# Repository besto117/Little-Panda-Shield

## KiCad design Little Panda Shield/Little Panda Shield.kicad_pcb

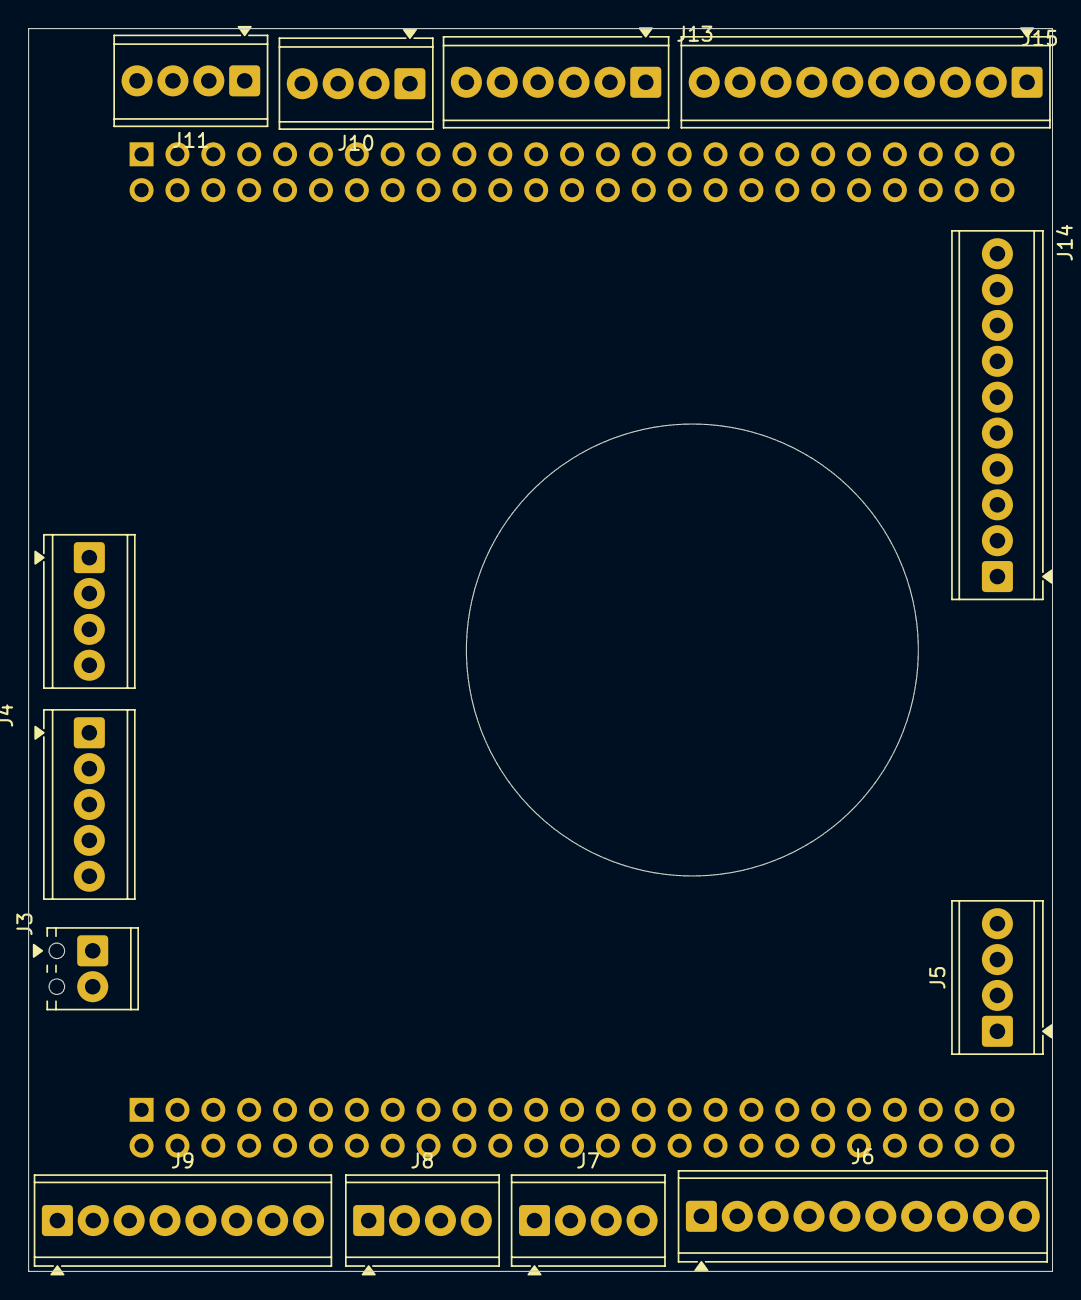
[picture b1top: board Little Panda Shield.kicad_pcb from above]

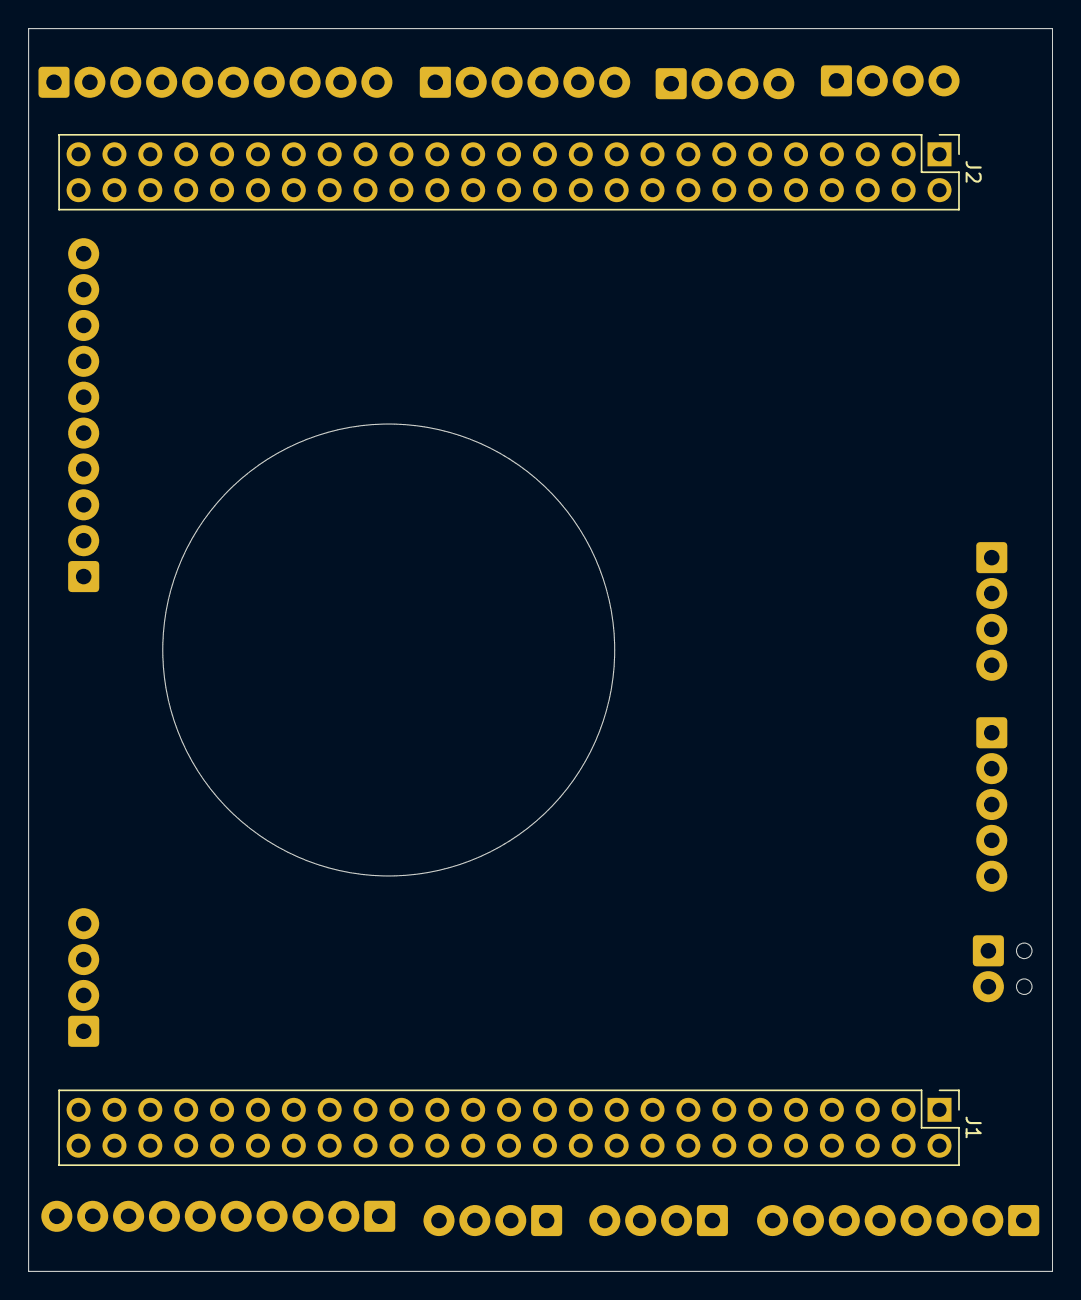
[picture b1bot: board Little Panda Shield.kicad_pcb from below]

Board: 2 copper layers, 72.5 x 88.0 mm, 15 parts (2 on the bottom side), 55 nets, no tracks yet.

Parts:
J1, J2: Conn_02x25_Top_Bottom; PinHeader_2x25_P2.54mm_Vertical
J3: Screw_Terminal_01x02; TerminalBlock_Phoenix_MPT-0,5-2-2.54_1x02_P2.54mm_Horizontal
J4: Screw_Terminal_01x05; TerminalBlock_Phoenix_MPT-0,5-5-2.54_1x05_P2.54mm_Horizontal
J5, J7, J8, J11, J12: Screw_Terminal_01x04; TerminalBlock_Phoenix_MPT-0,5-4-2.54_1x04_P2.54mm_Horizontal
J6, J14, J15: Screw_Terminal_01x10; TerminalBlock_Phoenix_MPT-0,5-10-2.54_1x10_P2.54mm_Horizont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
J9: Screw_Terminal_01x08; TerminalBlock_Phoenix_MPT-0,5-8-2.54_1x08_P2.54mm_Horizontal
J10: Screw_Terminal_01x08; TerminalBlock_Phoenix_MPT-0,5-4-2.54_1x04_P2.54mm_Horizontal
J13: Screw_Terminal_01x06; TerminalBlock_Phoenix_MPT-0,5-6-2.54_1x06_P2.54mm_Horizontal

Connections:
/1V8: J1.23, J4.3, J7.1
/3V3: J1.13, J1.15, J2.3, J2.5, J4.2, J9.1, J11.3
/5V: J1.45, J2.7, J2.9, J2.21, J2.47, J2.49, J4.4, J5.4, J11.4, J13.6
/AUTO: J1.11, J9.2
/CS: J2.17, J10.1
/CTS: J1.32, J6.3
/D0: J2.27, J14.1
/D1: J2.29, J14.2
/D2: J2.31, J14.3
/D3: J2.33, J14.4
/D4: J2.35, J14.5
/D5: J2.37, J14.6
/D6: J2.39, J14.7
/D7: J2.28, J14.8
/D8: J2.30, J14.9
/D9: J2.32, J14.10
/D10: J2.34, J15.1
/D11: J2.36, J15.2
/D12: J2.38, J15.3
/D13: J2.40, J15.4
/D18: J2.41, J15.5
/D19: J2.43, J15.6
/D20: J2.45, J15.7
/D21: J2.42, J15.8
/D22: J2.44, J15.9
/D23: J2.46, J15.10
/D+: J1.43, J5.2
/D-: J1.41, J5.3
/DCD: J1.35, J6.6
/DC_IN: J1.47, J1.49, J3.1
/DSR: J1.36, J6.5
/DTR: J1.29, J6.9
/GND: J1.1, J1.2, J1.17, J1.18, J1.20, J1.22, J1.24, J1.28, J1.39, J1.40, J1.42, J1.44, J1.46, J1.48, J1.50, J2.2, J2.4, J2.6, J2.8, J2.10, J2.11, J2.25, J2.48, J2.50, J3.2, J4.1, J4.5, J5.1, J6.1, J7.4, J9.8, J10.4, J11.1, J12.1, J12.2, J12.3, J12.4, J13.5
/MISO: J2.15, J2.22, J10.2, J13.2
/MOSI: J2.12, J2.23, J13.1
/RESET: J2.26, J13.4
/RI: J1.30, J6.2
/RST: J1.4, J9.3
/RTC: J2.1, J11.2
/RTS: J1.34, J6.4
/RXD: J1.33, J6.7
/S0: J1.7, J9.4
/S3: J1.8, J9.5
/S4: J1.5, J9.6
/S GND: J1.27, J6.10
/SCK: J2.24, J13.3
/SCL: J1.19, J7.3
/SDA: J1.21, J7.2
/SPL+: J1.14, J8.3
/SPL-: J1.16, J8.4
/SPR+: J1.10, J8.1
/SPR-: J1.12, J8.2
/SW: J1.3, J1.9, J9.7
/TXD: J1.31, J6.8
/WP: J2.13, J10.3
